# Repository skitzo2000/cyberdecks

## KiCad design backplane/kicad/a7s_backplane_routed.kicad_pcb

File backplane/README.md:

#  A7S Cyberdeck Backplane

A hand-solderable backplane **shield for the [Radxa Cubie A7S](https://radxa.com/products/cubie/a7s/)**
(Allwinner A733). It fans the A7S's 45 header pins out into a cyberdeck I/O board: dual swappable
radios, an input MCU, a touchscreen, and a Flipper-compatible expansion header.

> **Current board: v2** — schematic/netlist complete; PCB placed and **fully routed** (0 unconnected);
> **DRC-clean**; fab package generated. It corrects the header-mirror short that made the earlier boards
> DOA (see [What v2 fixed](#what-v2-fixed)). **Not yet fab-verified** — order it and it should power on.

| | File |
|---|---|
| **Board (v2)** | [`kicad/a7s_backplane_routed.kicad_pcb`](kicad/a7s_backplane_routed.kicad_pcb) |
| **Fab package** | [`kicad/a7s_backplane_v2_fab.zip`](kicad/a7s_backplane_v2_fab.zip) — upload to JLCPCB/PCBWay |
| **Schematic (editable)** | [`a7s_backplane.kicad_sch`](a7s_backplane.kicad_sch) · [PDF](a7s_backplane_schematic_kicad.pdf) |
| **Renders** | [`kicad/renders/routed_top.png`](kicad/renders/routed_top.png) · [`routed_bottom.png`](kicad/renders/routed_bottom.png) |

---

## What v2 fixed

The earlier boards (archived in [`v1/`](v1/)) mated the A7S GPIO headers **mirrored** — the shield's
socket pin 1 landed where the A7S's pin 30 is. That put the A7S **+3V3 rail onto the shield's GND**, so
the SBC dead-shorted and went dark the instant the shield was seated. v2 corrects it:

- **30-pin (double) header → NORTH edge, 15-pin (single) → SOUTH edge, both mirrored east-west** so the
  socket now mates the A7S pin-for-pin (shield pad *P* → A7S pin *P*; grounds land on grounds).
- A7S cluster nudged **1.75 mm west** so the ethernet-port edge lines up with the PCB west edge (the
  board rests on/at the RJ45).
- Full silkscreen: every pin labeled tight to the pad, all grounds ringed.

The **electrical design (netlist / schematic / BOM) is unchanged** across all revs — only the layout and
this header-mate correction differ.

## Revisions

| Rev | Status | What | Where |
|---|---|---|---|
| **v2** | **current — routed, DRC-clean, fab-ready** | header-mirror fixed, A7S aligned to board edge, full silk | *this folder* |
| v1 | archived / **do not fab** | original rev1 (ports faced inward) + the rev2 respin — both still had the header-mirror short | [`v1/`](v1/) ([REV1](v1/REV1.md) · [REV2](v1/REV2.md)) |

**Shared electrical docs (apply to all revs):** [SCHEMATIC.md](SCHEMATIC.md) ·
[SCHEMATIC-DIAGRAM.md](SCHEMATIC-DIAGRAM.md) · [BACKPLANE-DESIGN.md](BACKPLANE-DESIGN.md) ·
[BOM-SHIELD.md](BOM-SHIELD.md) · [BOM-DECK.md](BOM-DECK.md)

---

## Features

| Block | Detail |
|---|---|
| **2× "8+1" radio sockets** | Shared SPI1. Drop-in for **nRF24L01+ / CC1101 / CC2500** (8-pin nRF24 pin order + an AUX pin 9 for ESP-01 / breadboard use). Both radios can run simultaneously. |
| **RP2040-Zero input MCU** | Human inputs **only** — 4 on-board buttons + 2 off-board, joystick, rotary encoder. It is *not* a radio bridge; every radio line maps straight to an A7S header pin. |
| **2.8" SPI TFT** | ILI9341 display with resistive (XPT2046) touch. |
| **Flipper GPIO header** | Real two-connector layout (1×8 + 1×10, 17.78 mm gap) as a **female socket**, on the front, so genuine Flipper-ecosystem add-ons mate. |
| **Power** | Taps **5 V and 3V3 from the A7S header** (an external battery powers the A7S over its own USB-C port). Radio rails are polyfused. |

## Design choices

- **All through-hole / hand-solder.** No SMD, no pick-and-place — it's a backplane you solder to.
- **2-layer**, routed on both sides.
- Schematic/netlist generated with **[SKiDL](https://github.com/devbisme/skidl)** (the source of truth);
  board built/edited with the KiCad **pcbnew** Python API; autorouted headless with
  **[freerouting](https://github.com/freerouting/freerouting)**.
- A7S header geometry sits on **STEP-measured datums** (`refs/MECH-DATUMS.md`) so the shield mates correctly.

## Repository layout

```
README.md                     this index (v2)
a7s_backplane_skidl.py        netlist generator (SOURCE OF TRUTH)  ->  a7s_backplane.net
a7s_backplane.kicad_sch       editable KiCad schematic (generated from the netlist, opens in Eeschema)
a7s_backplane_schematic_kicad.{pdf,png}   schematic exports (for people without KiCad)
a7s_backplane_schematic.{svg,pdf,png}     graphviz connectivity/bus diagram
BACKPLANE-DESIGN.md           full design doc + pin maps   (shared across revs)
SCHEMATIC.md                  authoritative connectivity    (shared)
BOM-SHIELD.md / BOM-DECK.md   parts lists (sourcing links)  (shared)
kicad/
  build_pcb.py                netlist -> initial placement (pcbnew); config-driven
  a7s_backplane_routed.kicad_pcb   THE v2 board (routed, labeled, outline closed)
  a7s_backplane_v2_fab.zip    gerbers + drills, ready to order
  fab_v2/                     unzipped fab outputs
  renders/                    3D top/bottom renders of v2
  pipeline/                   this session's working intermediates (placement/route steps)
  3d/                         STEP models (gitignored; large)
a7s.pretty/                   custom footprints (TFT, RP2040-Zero, Flipper — see ATTRIBUTION.md)
refs/                         measured mechanical datums
tools/                        kpython (runs pcbnew against nix KiCad libs) + gen_kicad_schematic.py
v1/                           ARCHIVE — old rev1 + rev2 boards/gerbers/fab/renders. Do not fab.
```

## Build / regenerate

> **Full step-by-step + the exact scripts:** [`kicad/pipeline/README.md`](kicad/pipeline/README.md).
> It documents precisely how v2 was made (header-mirror fix → hand-placement → re-net → freerouting →
> silk → schematic → fab) with the one-off scripts in `kicad/pipeline/scripts/` and every gotcha.

The electrical design lives in SKiDL; the **placement is hand-done in KiCad** (the autoplacer output is
only a rough starting point). Quick version:

```sh
# 1. netlist (after editing the schematic)  ->  a7s_backplane.net
docker run --rm -e HOME=/tmp -v "$PWD":/work -w /work a7s-skidl python3 a7s_backplane_skidl.py

# 2. editable KiCad schematic from the netlist (derived artifact)
#    (needs kiutils + KICAD_SYM; see tools/gen_kicad_schematic.py header)
python3 tools/gen_kicad_schematic.py            # -> a7s_backplane.kicad_sch

# 3. board: build_pcb.py gives a rough placement; the real layout is hand-edited in pcbnew.
#    Then route headless (freerouting must run FOREGROUND):
freerouting -de kicad/a7s_backplane_v2.dsn -do kicad/a7s_backplane_v2.ses -mp 15
#    ...and import the .ses back with pcbnew.ImportSpecctraSES.
#    NOTE: ImportSpecctraSES silently drops Edge.Cuts segments — re-verify the outline is closed.

# 4. fab package
kicad-cli pcb export gerbers -o kicad/fab_v2/ kicad/a7s_backplane_routed.kicad_pcb
kicad-cli pcb export drill   -o kicad/fab_v2/ kicad/a7s_backplane_routed.kicad_pcb
```

> Do **not** re-run `build_pcb.py` against a placed/routed board — it emits a rough placed-but-unrouted
> board and discards the hand-placement + routing.

## Additional Notes

I think the radio headers belong in the left top corner so that any radio chips you plug in will be standing up vertically behind the deck & 90 degrees from the flipper headers becuase radio likes angles.

Yes its a lot of IO, I wanted to max out what was available in the friendliest way possible supporting cheap available modules that already exist in the market.

## Credits

Flipper GPIO footprints from **[kbembedded/flipper-gpio-eda](https://github.com/kbembedded/flipper-gpio-eda)**
(BSD-2-Clause) — see [`a7s.pretty/ATTRIBUTION.md`](./a7s.pretty/ATTRIBUTION.md). All other footprints are
original to this project.

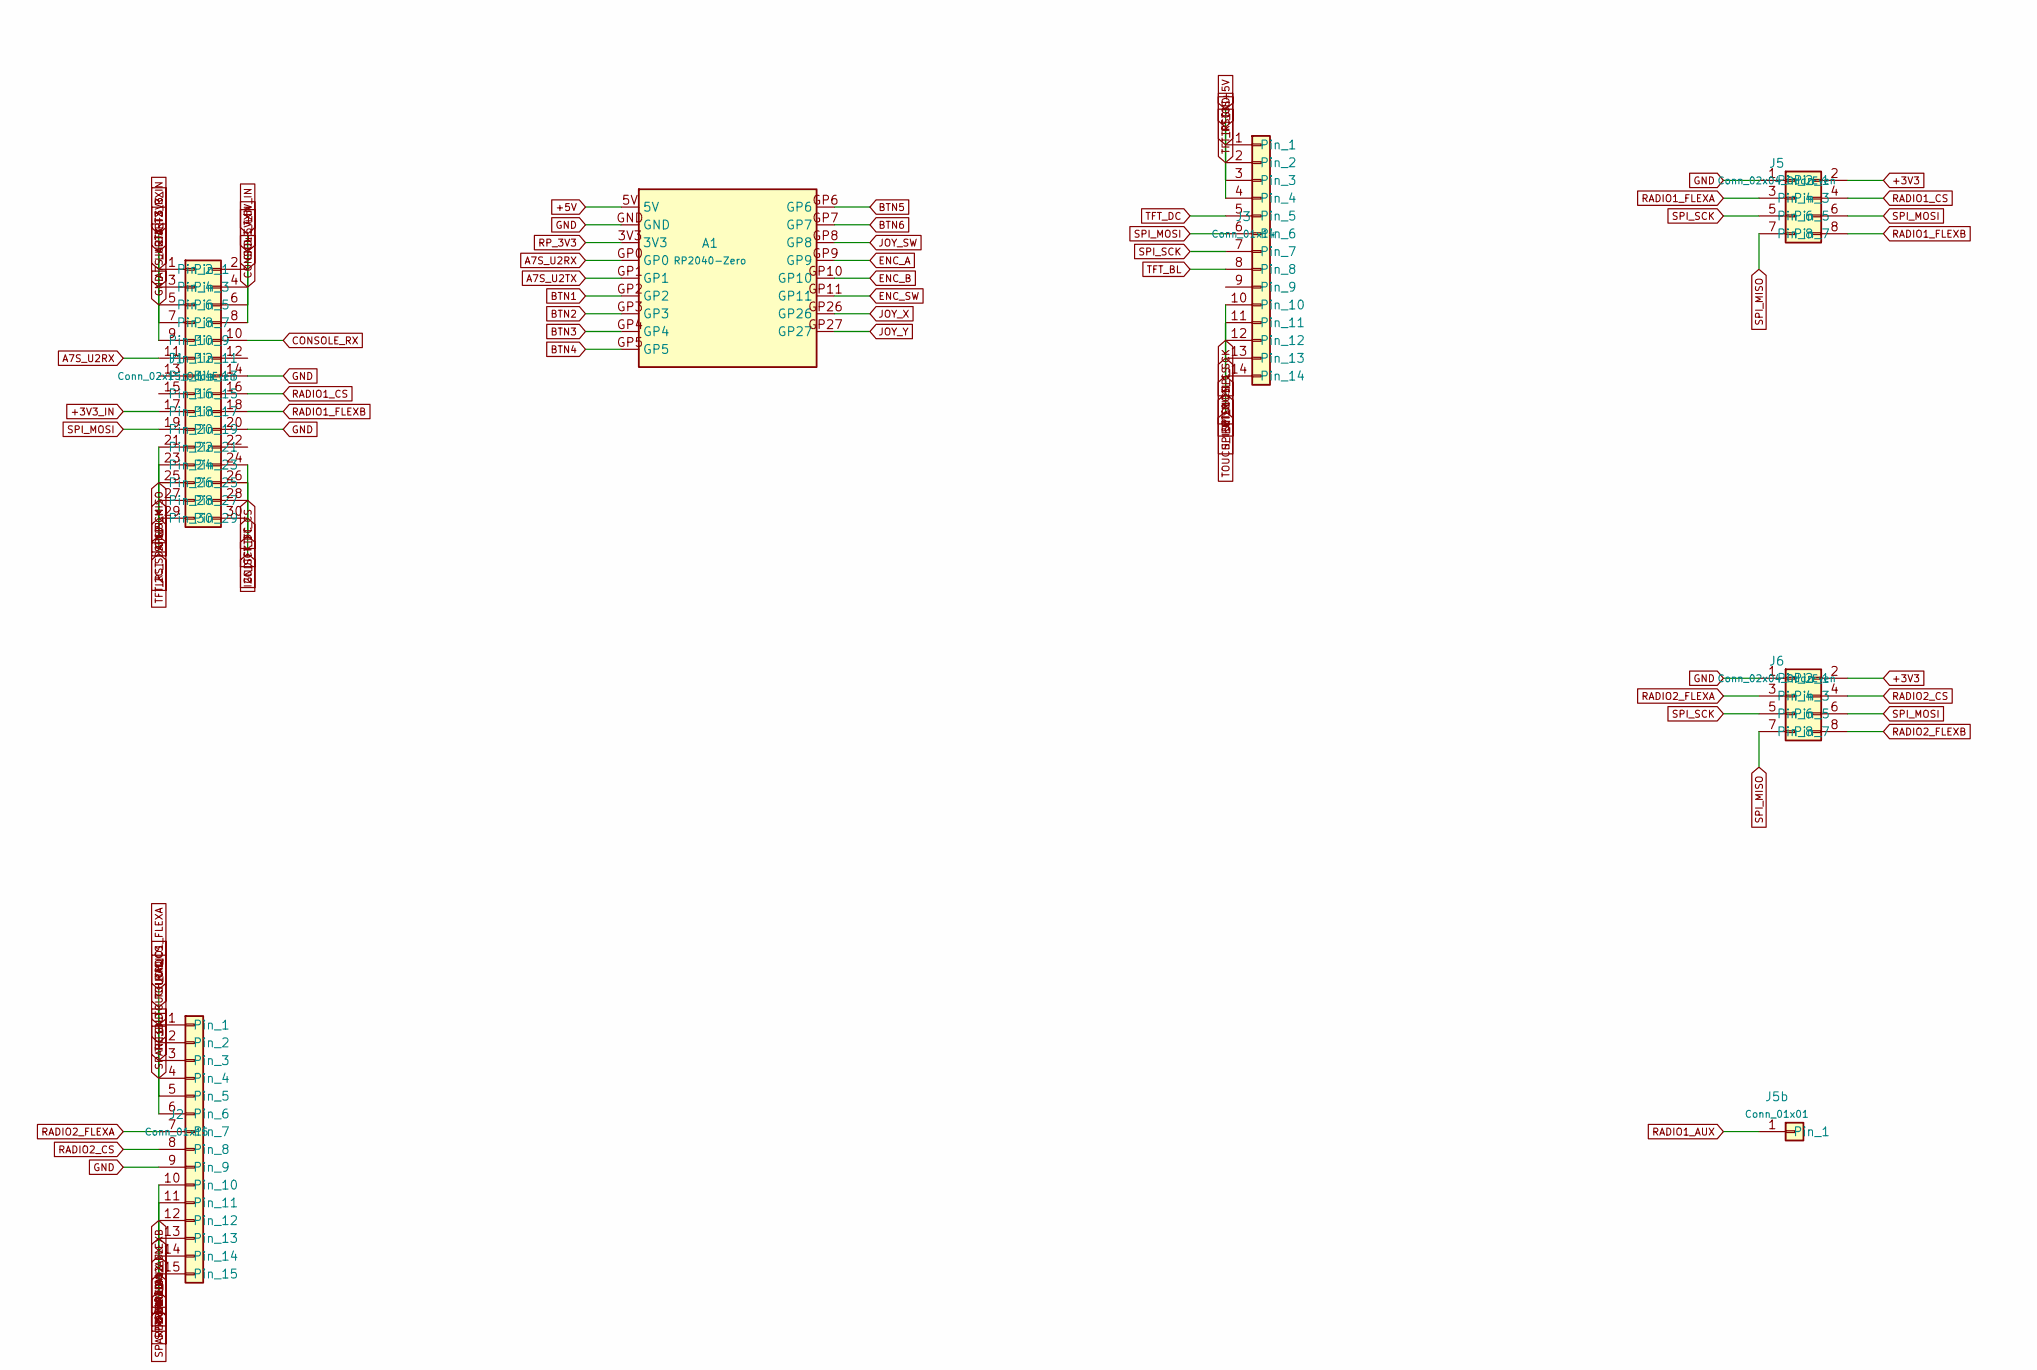
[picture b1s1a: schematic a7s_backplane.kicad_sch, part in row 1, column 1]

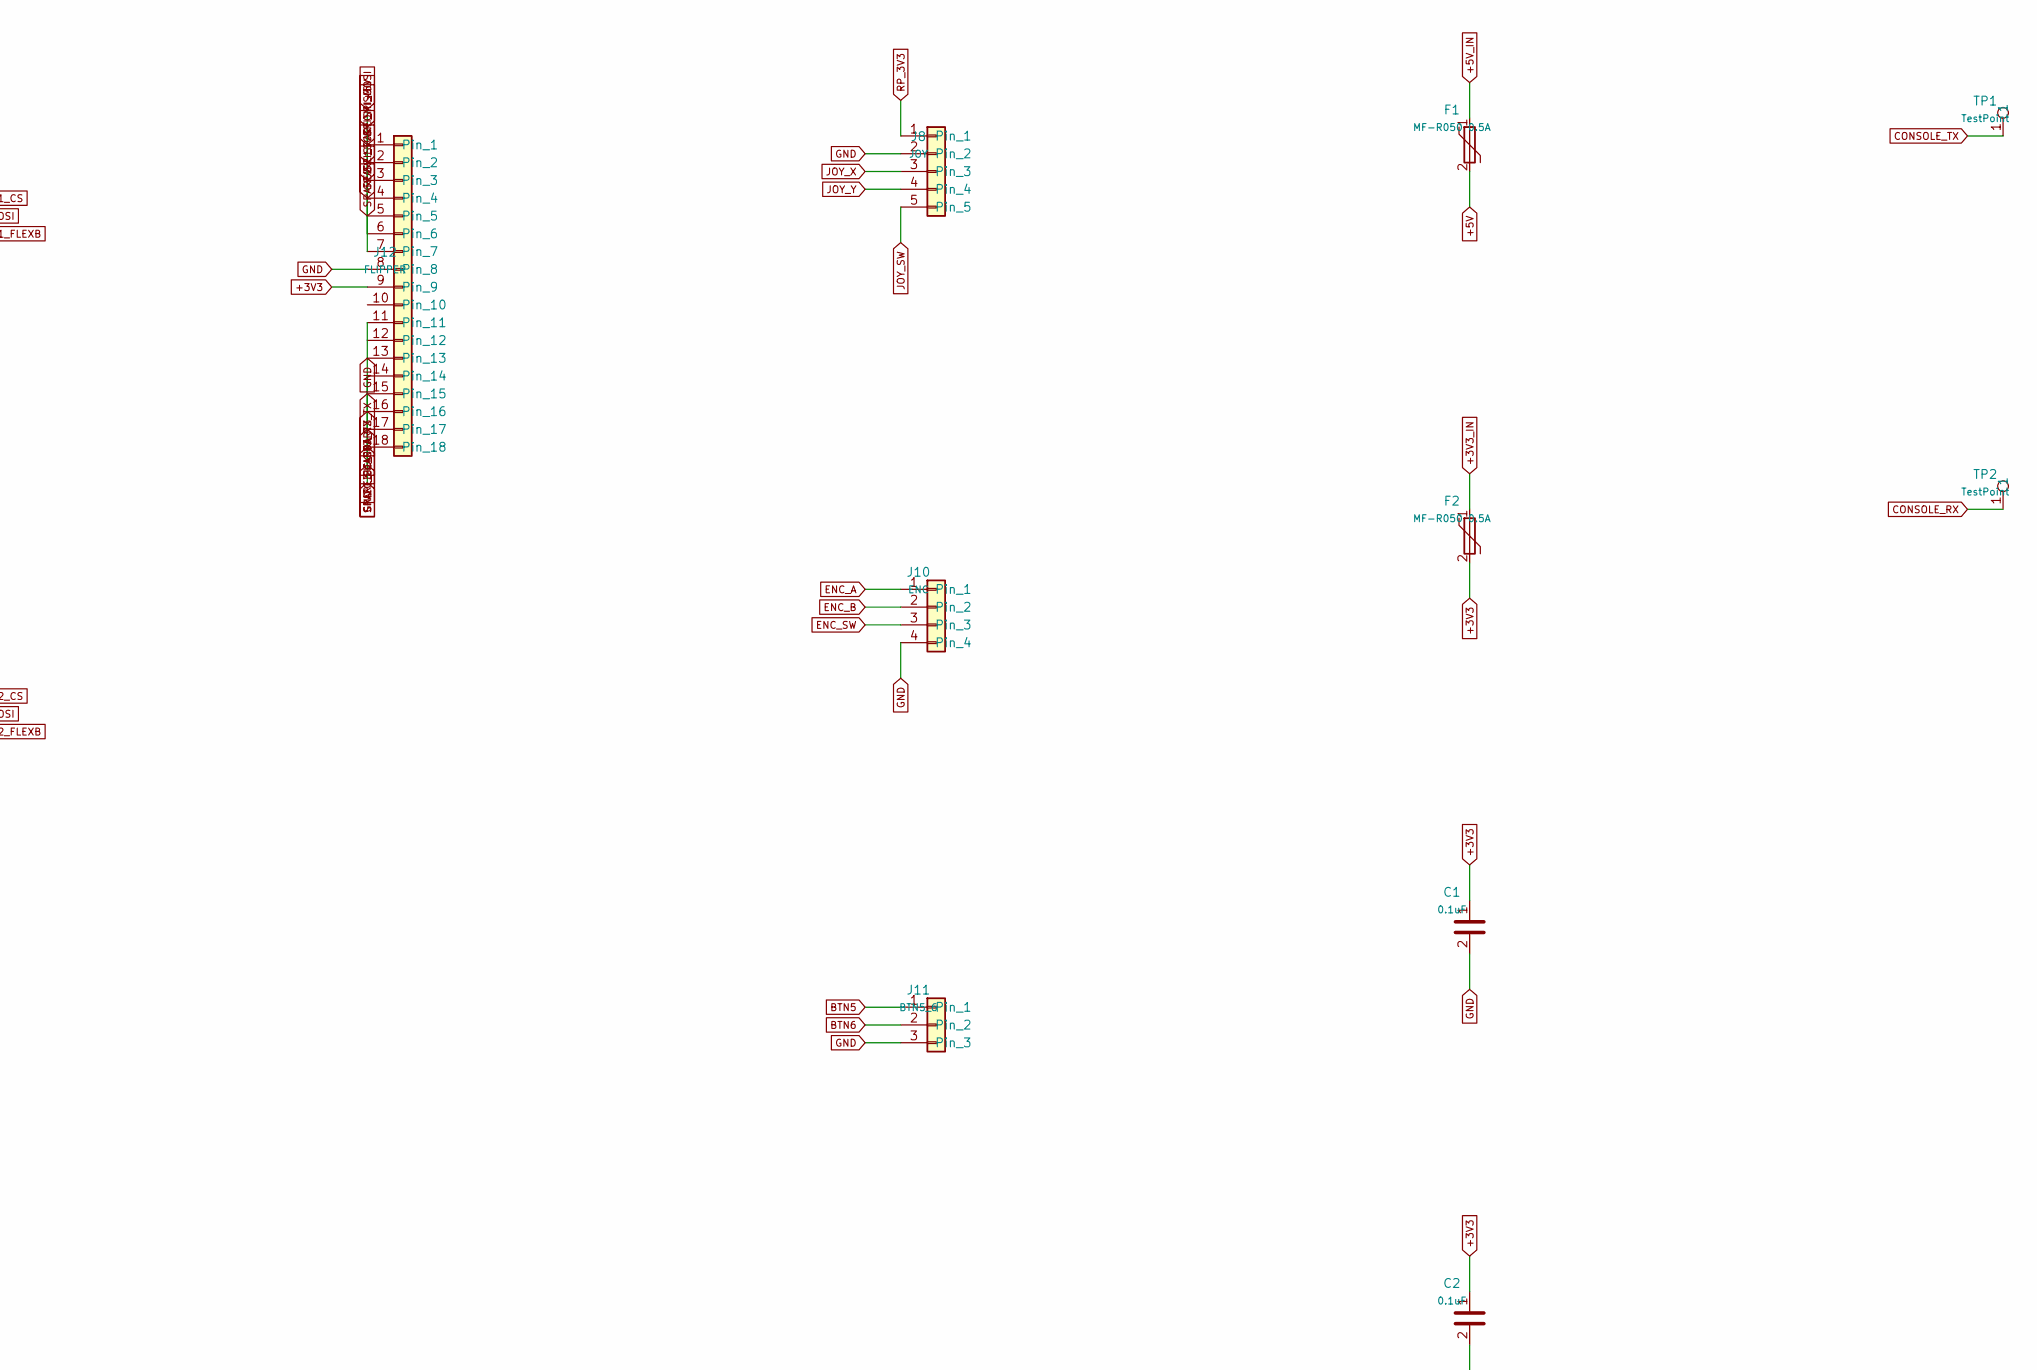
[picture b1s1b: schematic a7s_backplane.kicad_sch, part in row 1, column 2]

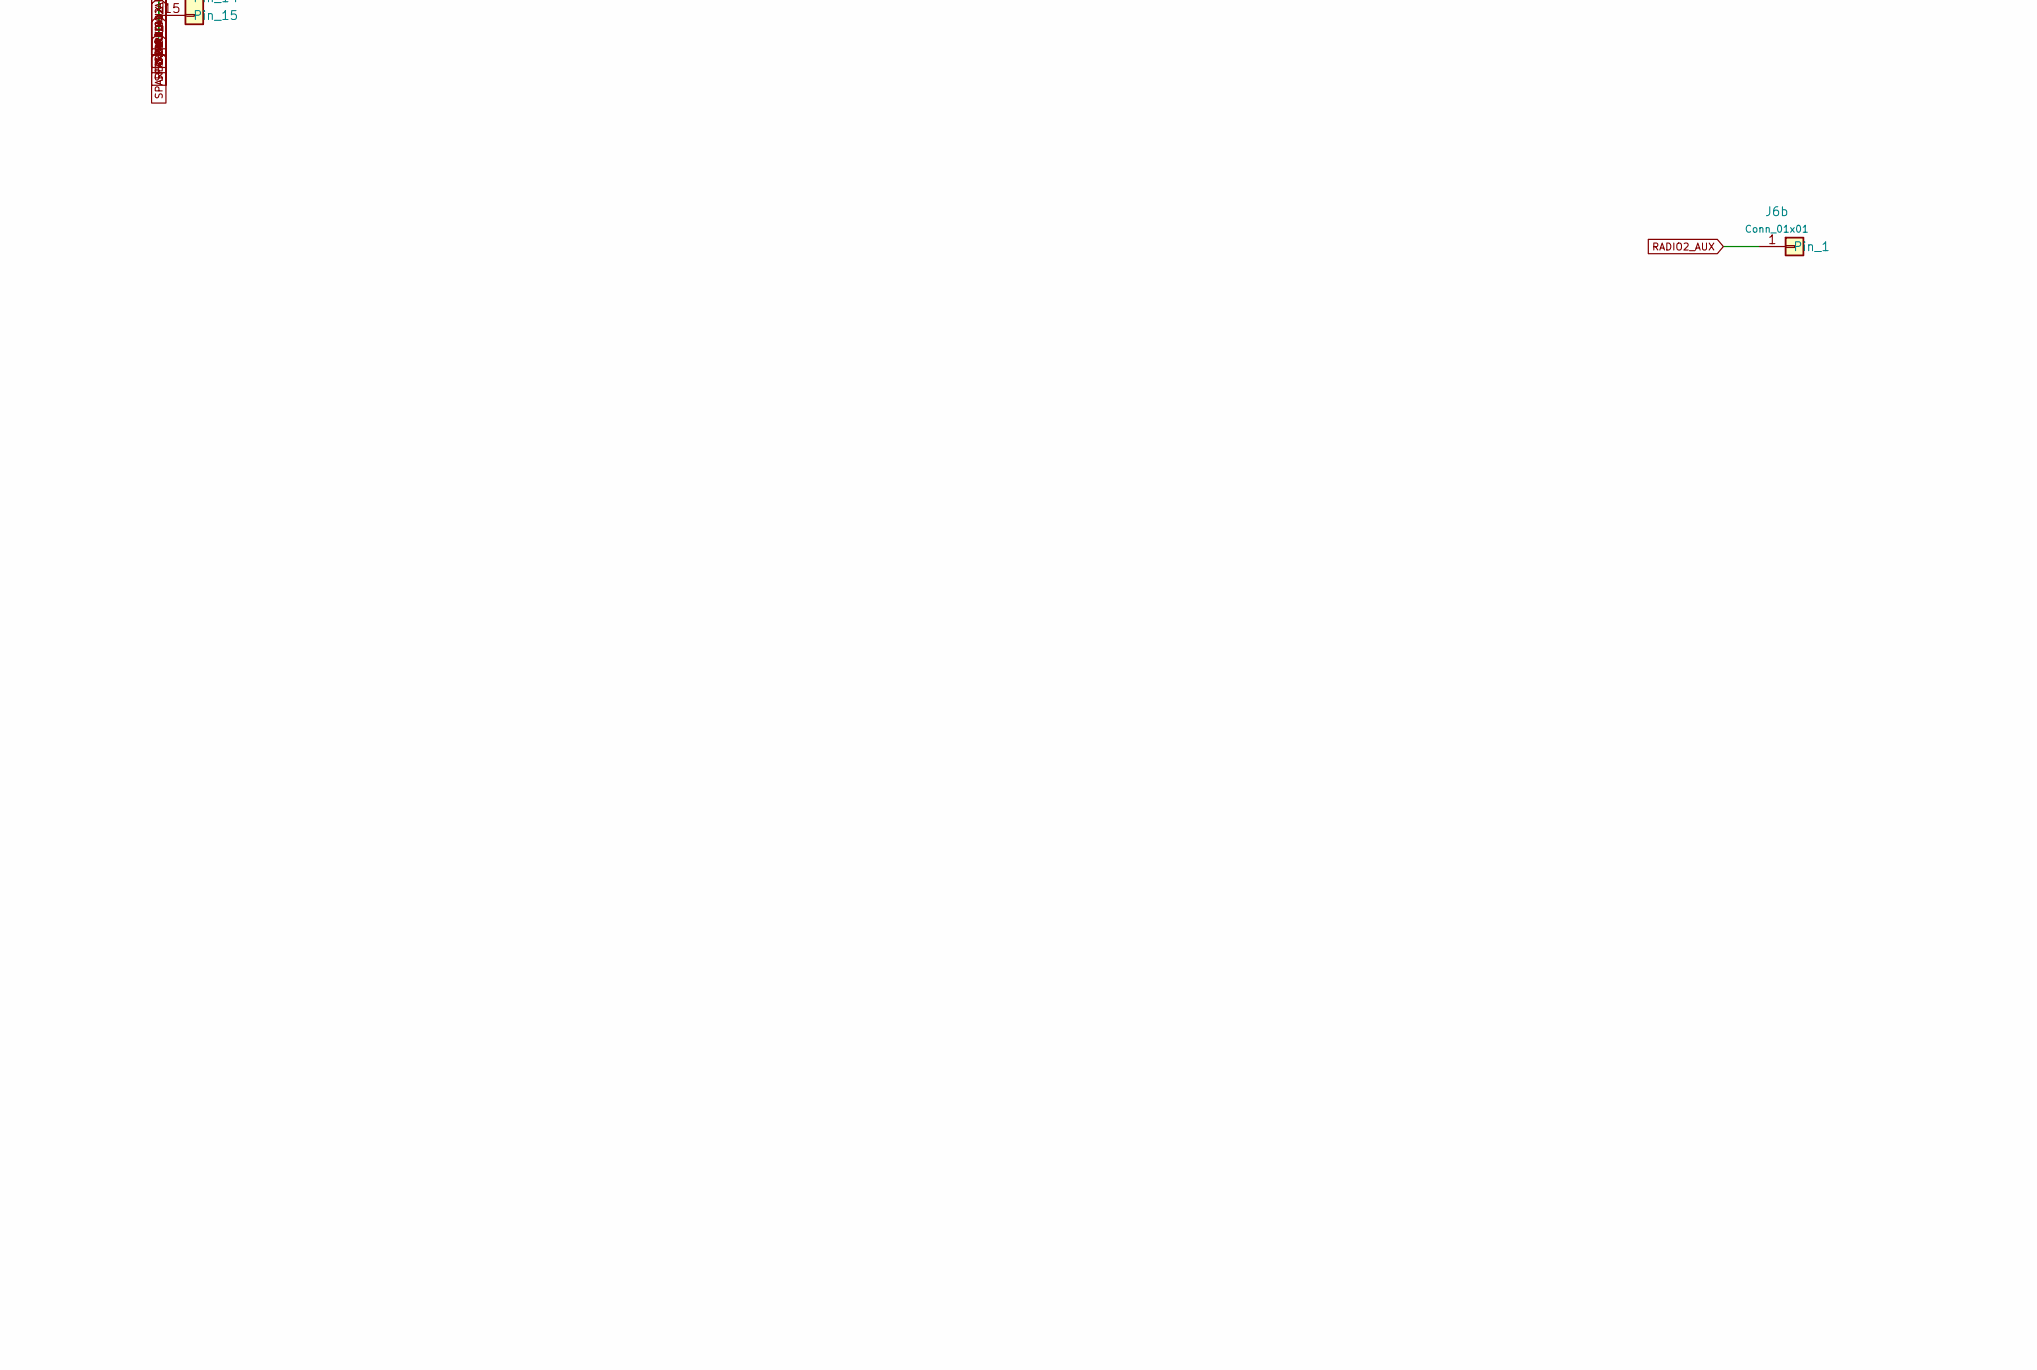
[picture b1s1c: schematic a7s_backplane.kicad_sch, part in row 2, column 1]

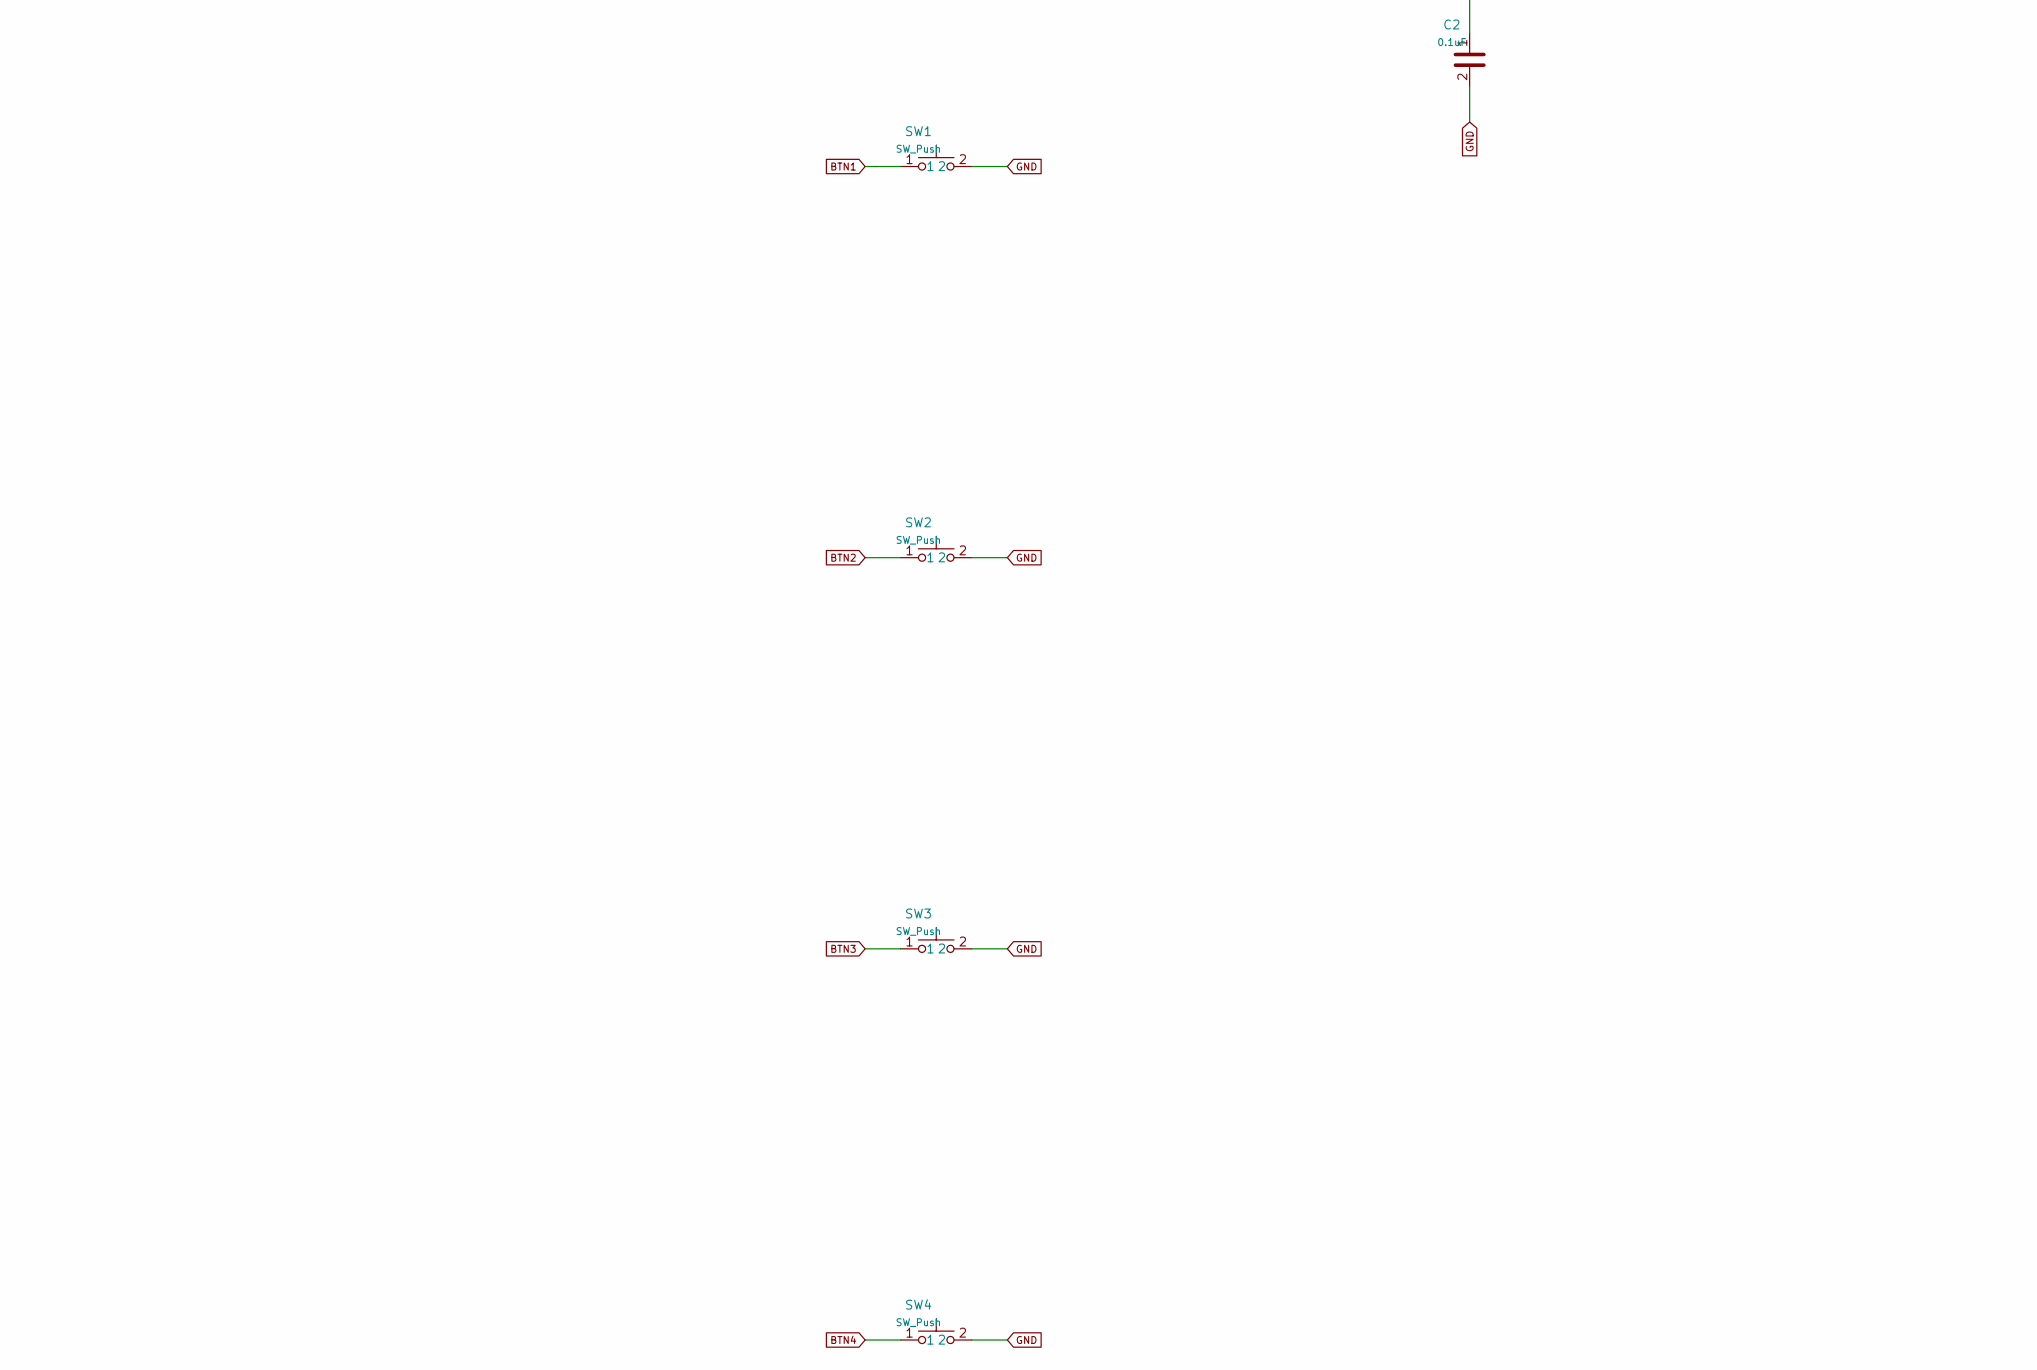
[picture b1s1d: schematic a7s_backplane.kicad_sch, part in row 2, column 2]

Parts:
A1: RP2040-Zero
C1, C2: 0.1uF
F1, F2: MF-R050 0.5A
J1: Conn_02x15_Odd_Even
J2: Conn_01x15
J3: Conn_01x14
J5, J6: Conn_02x04_Odd_Even
J5b, J6b: Conn_01x01
J8: JOY
J10: ENC
J11: BTN5_6
J12: FLIPPER
SW1, SW2, SW3, SW4: SW_Push
TP1, TP2: TestPoint

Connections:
+3V3: C1.1, C2.1, F2.2, J5.2, J6.2, J12.9
A7S_U2RX: A1.GP0, J1.11
BTN1: A1.GP2, SW1.1
BTN2: A1.GP3, SW2.1
BTN3: A1.GP4, SW3.1
BTN4: A1.GP5, SW4.1
BTN5: A1.GP6, J11.1
BTN6: A1.GP7, J11.2
CONSOLE_RX: J1.10, TP2.1
ENC_A: A1.GP9, J10.1
ENC_B: A1.GP10, J10.2
ENC_SW: A1.GP11, J10.3
JOY_SW: A1.GP8, J8.5
JOY_X: A1.GP26, J8.3
JOY_Y: A1.GP27, J8.4
RADIO1_CS: J1.16, J5.4
RADIO1_FLEXB: J1.18, J5.8
RADIO2_CS: J2.8, J6.4
RADIO2_FLEXA: J2.7, J6.3
RP_3V3: A1.3V3, J8.1

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
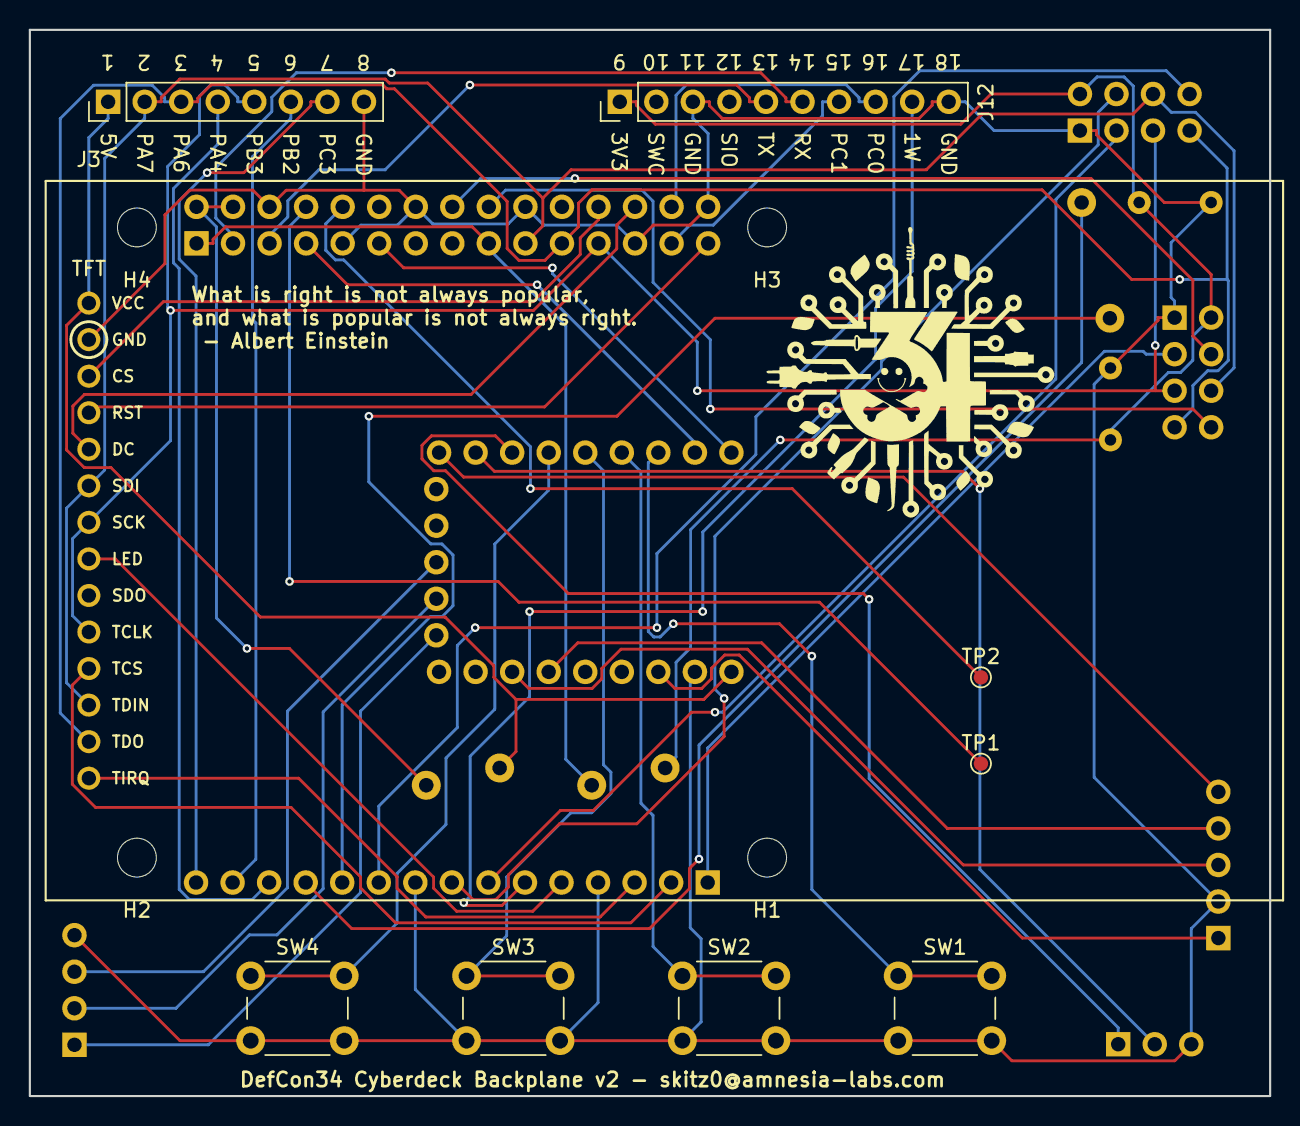
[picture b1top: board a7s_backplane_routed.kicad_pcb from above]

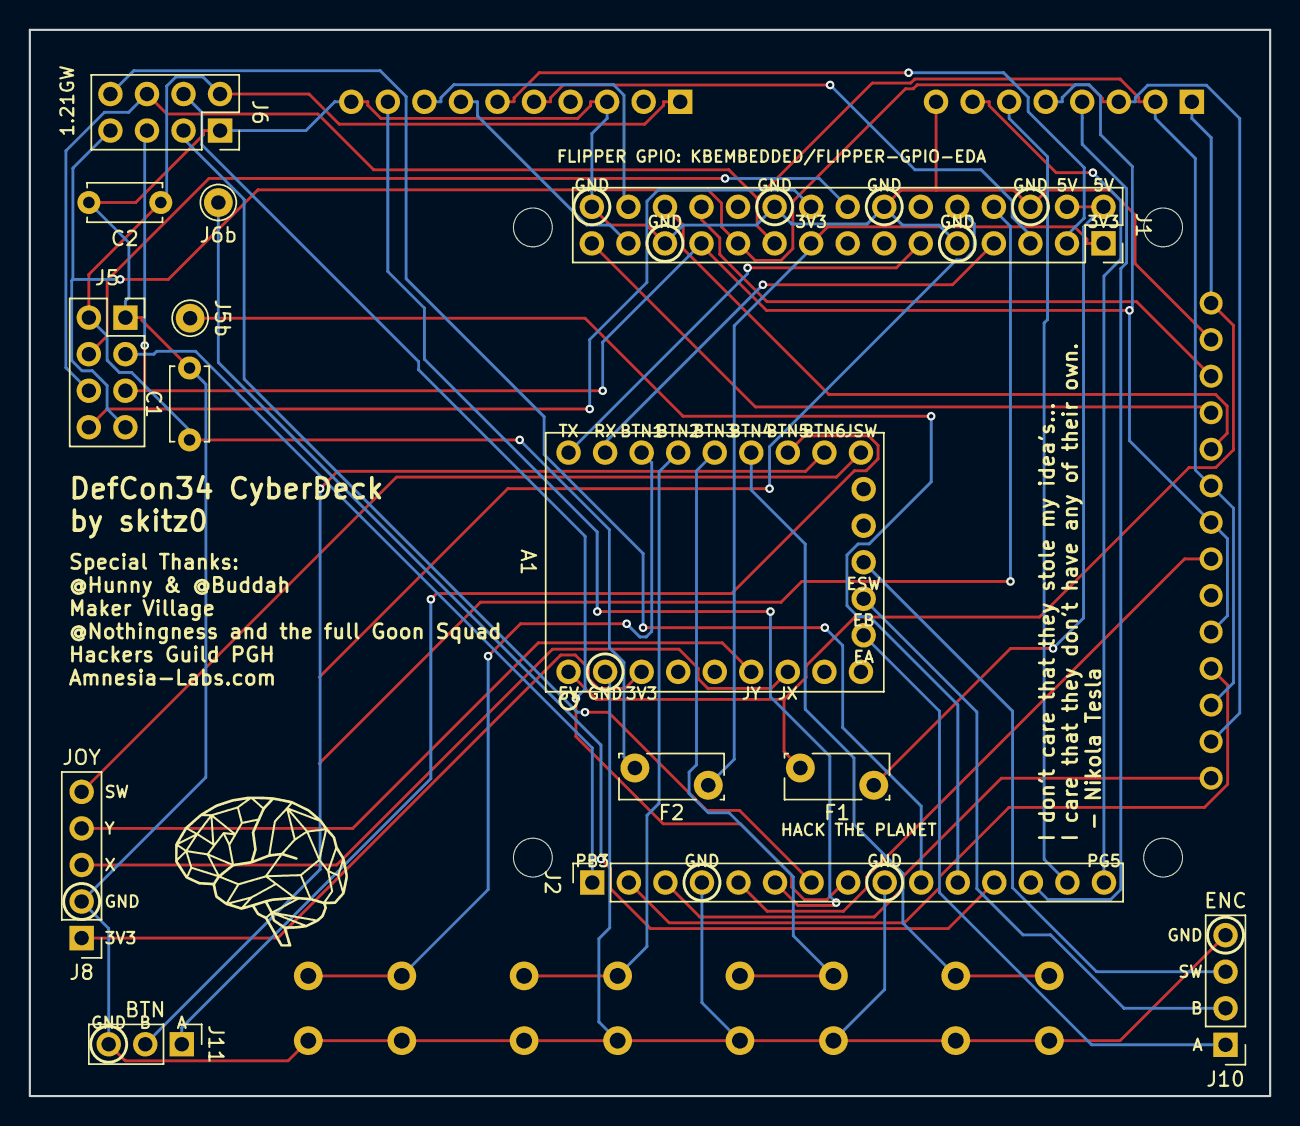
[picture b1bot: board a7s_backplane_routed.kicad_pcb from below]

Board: 2 copper layers, 86.2 x 74.1 mm, 26 parts (14 on the bottom side), 47 nets.

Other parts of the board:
H1, H2, H3, H4: MountingHole_2.7mm_M2.5

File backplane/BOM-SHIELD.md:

# Shield BOM — A7S Cyberdeck Backplane

Parts to populate the **backplane PCB itself**. Derived from the live netlist
(`a7s_backplane.net`) — all through-hole, no SMD, no ICs, no resistors.

**Mounting side:** connector headers (J1/J2, J5/J6, J8, J10, J11) and the RP2040 are on the **back**;
the screen, Flipper socket, and the 4 push-buttons are on the **front**.

- **No prices here** — this is a parts list to start sourcing from.
- **Sourcing links are options for review, not picks.** Each links a search/category or a
  canonical product page so you can choose the exact part. Confirm pitch, pin count, and
  (for the headers) pin-1 orientation against the board before buying.
- Off-board input *modules* (thumbstick, encoder, aux buttons) and the *radio modules* live in
  the **[deck BOM](./BOM-DECK.md)** — the shield only carries their headers/sockets.

## PCB

| Item | Spec | Qty | Sourcing options |
|---|---|--:|---|
| Backplane PCB | 2-layer, ~86 × 74 mm, THT, custom outline | 1 | [JLCPCB](https://jlcpcb.com/) · [PCBWay](https://www.pcbway.com/) · [OSH Park](https://oshpark.com/) |

## Connectors that mate the A7S

| Ref | Item | Spec / package | Qty | Sourcing options |
|---|---|---|--:|---|
| J1 | Female header 2×15 (30-pin) | 2.54 mm, THT | 1 | [LCSC](https://www.lcsc.com/search?q=2x15%20female%20header%202.54) · [DigiKey](https://www.digikey.com/en/products/result?keywords=2x15%20f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 · [Amazon](https://www.amazon.com/s?k=2x15+female+pin+header+2.54mm) |
| J2 | Female header 1×15 (15-pin) | 2.54 mm, THT | 1 | [LCSC](https://www.lcsc.com/search?q=1x15%20female%20header%202.54) · [DigiKey](https://www.digikey.com/en/products/result?keywords=1x15%20f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 · [Amazon](https://www.amazon.com/s?k=1x15+female+pin+header+2.54mm) |

> J1/J2 are the sockets that press onto the A7S male GPIO headers — verify pin length and **pin-1 end** before ordering (see `refs/MECH-DATUMS.md`).

## Radio sockets (the "8+1")

| Ref | Item | Spec / package | Qty | Sourcing options |
|---|---|---|--:|---|
| J5, J6 | Female header 2×4 (8-pin socket) | 2.54 mm, THT | 2 | [LCSC](https://www.lcsc.com/search?q=2x4%20female%20header%202.54) · [DigiKey](https://www.digikey.com/en/products/result?keywords=2x4%20fe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 · [Amazon](https://www.amazon.com/s?k=2x4+8pin+female+header+2.54mm) |
| J5b, J6b | Female header 1×1 (AUX / pin 9) | 2.54 mm, THT | 2 | [LCSC](https://www.lcsc.com/search?q=1x1%20female%20header%202.54) · [Amazon](https://www.amazon.com/s?k=single+pin+female+header+2.54mm) |

## Display

| Ref | Item | Spec / package | Qty | Sourcing options |
|---|---|---|--:|---|
| J3 | 2.8" SPI TFT, ILI9341 + XPT2046 resistive touch | 14-pin SPI module | 1 | [AliExpress](https://www.aliexpress.com/w/wholesale-2.8-inch-SPI-TFT-ILI9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 · [Amazon](https://www.amazon.com/s?k=2.8+inch+SPI+TFT+ILI9341+XPT2046+touch) |
| — | Female header 1×14 *(only if socketing the TFT)* | 2.54 mm, THT | 1 | [LCSC](https://www.lcsc.com/search?q=1x14%20female%20header%202.54) · [Amazon](https://www.amazon.com/s?k=1x14+female+header+2.54mm) |

## Input MCU

| Ref | Item | Spec / package | Qty | Sourcing options |
|---|---|---|--:|---|
| A1 | Waveshare RP2040-Zero | castellated module, soldered | 1 | [Waveshare](https://www.waveshare.com/rp2040-zero.htm) · [Amazon](https://www.amazon.com/s?k=Waveshare+RP2040-Zero) · [AliExpress](https://www.aliexpress.com/w/wholesale-RP2040-Zero.html) |

> Confirm the RP2040-Zero **row spacing (assumed 15.24 mm)** against the footprint before fab.

## On-board buttons

| Ref | Item | Spec / package | Qty | Sourcing options |
|---|---|---|--:|---|
| SW1–SW4 | Tactile push button, 6 mm | THT, 4-leg | 4 | [LCSC](https://www.lcsc.com/search?q=6mm%20tactile%20switch%20throu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 · [DigiKey](https://www.digikey.com/en/products/result?keywords=6mm%20ta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 · [Amazon](https://www.amazon.com/s?k=6mm+tactile+push+button+through+hole) |

## Off-board input headers (solder fields — modules in the deck BOM)

| Ref | Item | Spec / package | Qty | Sourcing options |
|---|---|---|--:|---|
| J8 | 1×5 solder pads (analog joystick) | 2.54 mm THT holes | — | no part — solder wires directly |
| J10 | 1×4 solder pads (rotary encoder) | 2.54 mm THT holes | — | no part — solder wires directly |
| J11 | 1×4 solder pads (aux buttons 5/6) | 2.54 mm THT holes | — | no part — solder wires directly |

> **No headers here** — these are bare solder holes; the joystick/encoder/buttons are casing-mounted and
> wired straight to the pads (the modules themselves are in the [deck BOM](./BOM-DECK.md)).

## Flipper expansion header

| Ref | Item | Spec / package | Qty | Sourcing options |
|---|---|---|--:|---|
| J12 | **Female socket** 1×8 + 1×10 (Flipper GPIO, 17.78 mm gap), on the front | 2.54 mm, THT | 1 set | [LCSC](https://www.lcsc.com/search?q=1x10%20female%20header%202.54) · [DigiKey](https://www.digikey.com/en/products/result?keywords=1x8%20fe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 · [Amazon](https://www.amazon.com/s?k=2.54mm+female+header+single+row) |

> Two single-row **female** sockets matching the Flipper Zero top-edge GPIO layout — 1×8 + 1×10 with the
> 17.78 mm gap. (Footprint holes are shared with a male header, so the layout is the same either way.)

## Passives

| Ref | Item | Spec / package | Qty | Sourcing options |
|---|---|---|--:|---|
| C1, C2 | Ceramic capacitor, radio 3V3 decoupling (≈0.1 µF; add 1–10 µF if desired) | THT radial (D5 mm) | 2 | [LCSC](https://www.lcsc.com/search?q=0.1uF%20ceramic%20capacitor%20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 · [DigiKey](https://www.digikey.com/en/products/result?keywords=0.1uF%20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 |
| F1, F2 | Resettable polyfuse (PPTC), F1 = 5 V rail, F2 = 3V3 rail (≈0.5 A hold — confirm vs radio draw) | THT radial (Bourns MF-R) | 2 | [DigiKey](https://www.digikey.com/en/products/result?keywords=bourns%2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 · [Mouser](https://www.mouser.com/c/?q=MF-R%20polyfuse) · [LCSC](https://www.lcsc.com/search?q=PPTC%20resettable%20fuse%20thr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 |

## Misc / mechanical

| Ref | Item | Spec / package | Qty | Sourcing options |
|---|---|---|--:|---|
| TP1, TP2 | Test point / 1×1 header (UART console) *(optional)* | 2.54 mm, THT | 2 | [LCSC](https://www.lcsc.com/search?q=test%20point%20pad) · [Amazon](https://www.amazon.com/s?k=PCB+test+point+pin) |
| H1–H4 | M2.5 standoff + screw set (shield ↔ A7S, 43.8 mm square) | nylon/brass | 4 | [Amazon](https://www.amazon.com/s?k=M2.5+standoff+kit) · [DigiKey](https://www.digikey.com/en/products/result?keywords=M2.5%20s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 |

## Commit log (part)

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2026-05-20 Add BBQ20 keyboard module → RP2040 USB QMK daughterboard research
    BBQ20-DAUGHTERBOARD.md documents the 34-pin 0.5mm-pitch FFC pinout,
    RP2040 GPIO map, trackpad subsystem (1.8V I2C @ 0x3B), backlight
    driver, and full daughterboard BOM (LDOs, level shifters, FET,
    connector) for builders re-spinning a Solder-Party-equivalent
    carrier with raw BB Classic keyboard modules.
    refs/ captures the upstream Solder Party schematic (CERN-OHL v1.2)
2026-05-21 Add radio header board: 4-slot universal cyberdeck daughter-PCB
    Design doc for the radio carrier that mounts on the Pi 40-pin GPIO via
    14 mm stacking header (no blocking — next HAT stacks on top) and exposes
    four cheap-radio slots:
    A. CC1101 sub-GHz 1×8 socket (fixed, "always there" radio)
    B. HopeRF RFM95W/RFM69HCW 16-pin SMD castellated landing
    C. Universal 1×9 header, Adafruit LoRa Bonnet pin-compatible
2026-05-21 Pivot radio header board to slim pogo-pin two-piece architecture
    The v1 design used a 14 mm extra-tall stacking GPIO header (Adafruit
    2223) which added ~22 mm to the Pi+HAT vertical stack — too thick for
    a slab cyberdeck. Pivot to a PiSugar-3-style mount: a thin pogo-pin
    adapter (RHB-Pogo) snaps onto the BACK of the Pi via spring-loaded
    contacts on the GPIO solder-pad footprint, and a separate radio
    carrier (RHB-Carrier) lives elsewhere in the chassis connected by a
2026-06-19 Add A7S cyberdeck backplane (Radxa Cubie A7S radio/RP2040/TFT/Flipper shield)
    Hand-solder THT shield for the Radxa Cubie A7S: 2x '8+1' radio sockets
    (nRF24/CC1101/CC2500) on SPI1, RP2040-Zero input MCU, 2.8" ILI9341 TFT+touch,
    real two-connector Flipper GPIO header. SKiDL netlist + pcbnew board +
    freerouting. Schematic verified; layout is a routed WIP for human refinement.
    Flipper footprints from kbembedded/flipper-gpio-eda (BSD-2-Clause).
2026-06-19 backplane: expand README (build steps + pre-fab verification checklist)
2026-06-19 backplane: add shield + full-deck BOMs (sourcing links, no prices)
    BOM-SHIELD.md - PCB parts from the netlist (all-THT)
    BOM-DECK.md - full system (A7S, power, radios, inputs, chassis)
    Mark the old inline BACKPLANE-DESIGN.md BOM as superseded; link both from README.
2026-06-19 backplane: purge stale/confusing files; single canonical board
    Remove HANDOFF.md, STATUS.md, _routed duplicate, DRC/scratch outputs, KiCad
    lock/.prl files, 3D placeholder. Old §7 BOM table -> links to BOM-SHIELD/DECK.
    Add .gitignore so build scratch + lock files stay out.
2026-06-19 backplane: README — author notes (radio placement intent, IO rationale)
2026-06-19 backplane: README — disambiguate the 4 headers (radios 8+1 backside vs Flipper 1x8+1x10 front)
2026-06-19 backplane: add 3D render previews (real screen + RP2040-Zero STEP); embed in README
    Front: 2.8" TFT + buttons. Back: RP2040-Zero, radios standing, power.
    Rough render via kicad-cli + real STEP models. 3D working files gitignored.
2026-06-19 backplane: headers to back, Flipper female socket, inputs as solder pads; exploded assembly render with A7S; drop old half-view renders
2026-06-19 backplane: render — J12 as female socket, J8/J10/J11 as bare solder pads (matches design)
2026-06-19 backplane: render — flip A7S right-side-up (GPIO pins up; backplane mates from above)
2026-06-19 backplane: nicer assembly render (smooth-shaded, anti-aliased)
2026-06-19 backplane: clean kicad-cli renders (top deck-face + underside); add underside view, drop FreeCAD artifacts
2026-06-19 backplane: underside render — drop fake radio-module placeholders, show real sockets
2026-06-19 backplane: right-handed layout (A7S inverted, USB-C left); radios 90deg top-right; routed 0-unconnected; new renders
2026-06-20 backplane: validated radio spacing (6.3mm module clearance), re-routed 0-unconnected; board-only renders + module keep-out on Dwgs.User
2026-06-20 backplane: top render — see-through TFT, connector aligned to J3 header
